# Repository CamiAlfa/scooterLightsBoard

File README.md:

# scooterLightsBoard
Add lights to the scooter

Board files designed using kicad 6.

The board uses the internal 12 volts to enable a relay.
That relay enables the stepdown and the front light.
The stepdown is a 4,5-60V LM2596HV. It must be regulated to 12v (or whatever voltage needed) before instalation to avoid damage.

The frontlight needs a separate switch to activate it independently.

The inputs of the board are:
* (J1) Drv signals:
  1. 12v signal
  2. Gnd
  3. Tail light signal
* (J2) Battery power:
  1. Batt +
  2. Batt -

The outputs are:
* (J3) Frontlight:
  1. Batt + (relay)
  2. 12v
  3. Gnd
* (J5) 12V output:
  1. 12v
  2. Gnd
* (j4) Tail light:
  1. Tail light+ (12v)
  2. Tail light-

Schematic for reference:

Greetings from Spain

Camilo

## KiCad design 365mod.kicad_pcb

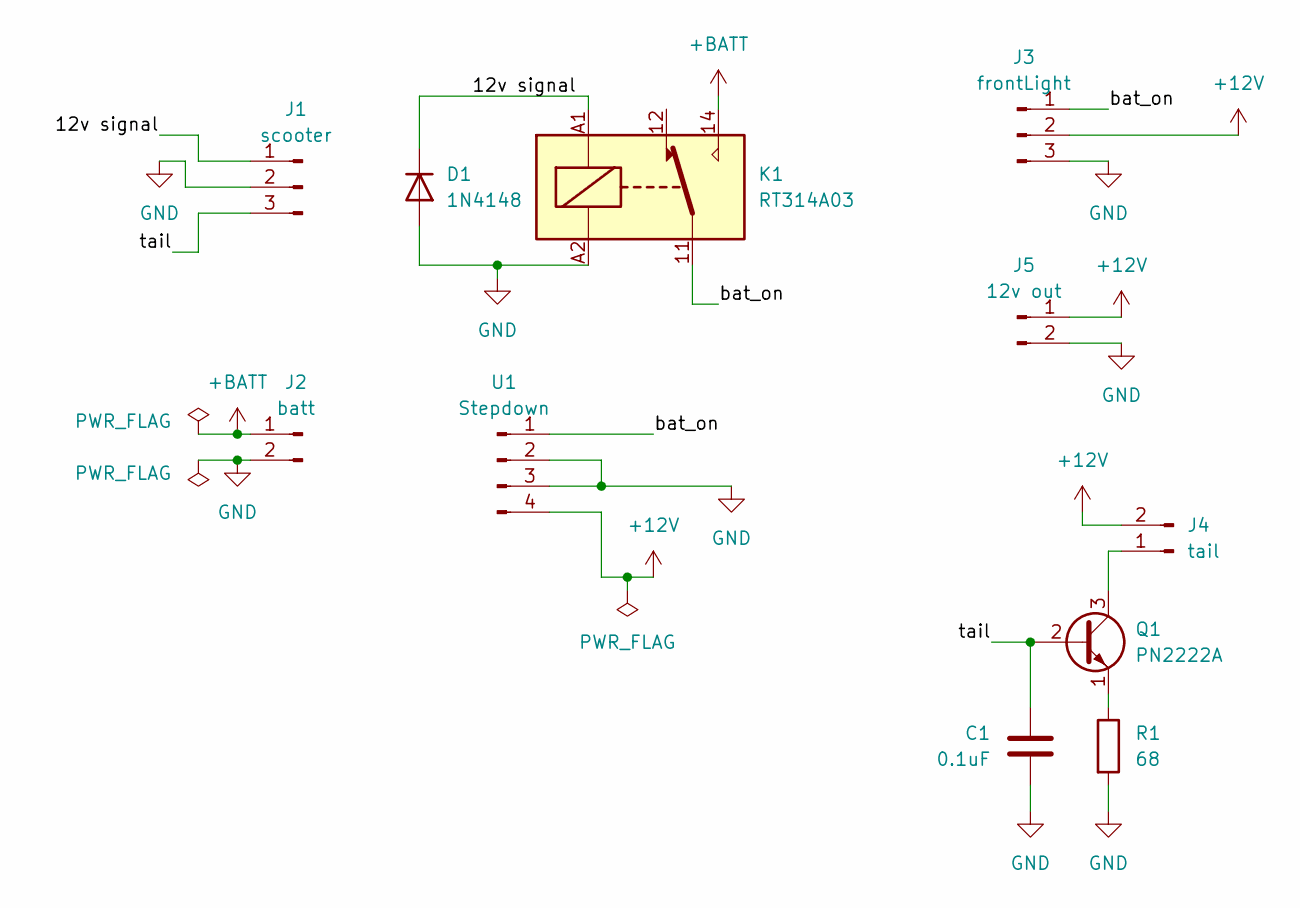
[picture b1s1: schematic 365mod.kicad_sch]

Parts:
C1: 0.1uF; C_Disc_D3.4mm_W2.1mm_P2.50mm
D1: 1N4148; D_DO-35_SOD27_P7.62mm_Horizontal
J1: scooter; PinHeader_1x03_P2.54mm_Vertical
J2: batt; PinHeader_1x02_P2.54mm_Vertical
J3: frontLight; PinHeader_1x03_P2.54mm_Vertical
J4: tail; PinHeader_1x02_P2.54mm_Vertical
J5: 12v out; PinHeader_1x02_P2.54mm_Vertical
K1: RT314A03; Relay_SPDT_Schrack-RT1-16A-FormC_RM5mm
Q1: PN2222A; TO-92_Inline
R1: 68; R_Axial_DIN0204_L3.6mm_D1.6mm_P2.54mm_Vertical
U1: Stepdown; DSN2596

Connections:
+12V: J3.2, J4.2, J5.1, U1.4
+BATT: J2.1, K1.14
/12v signal: D1.1 (K), J1.1, K1.A1
/bat_on: J3.1, K1.11, U1.1
/tail: C1.2, J1.3, Q1.2 (B)
GND: C1.1, D1.2 (A), J1.2, J2.2, J3.3, J5.2, K1.A2, R1.2, U1.2, U1.3
unnamed: J4.1, Q1.3 (C)
unnamed: Q1.1 (E), R1.1

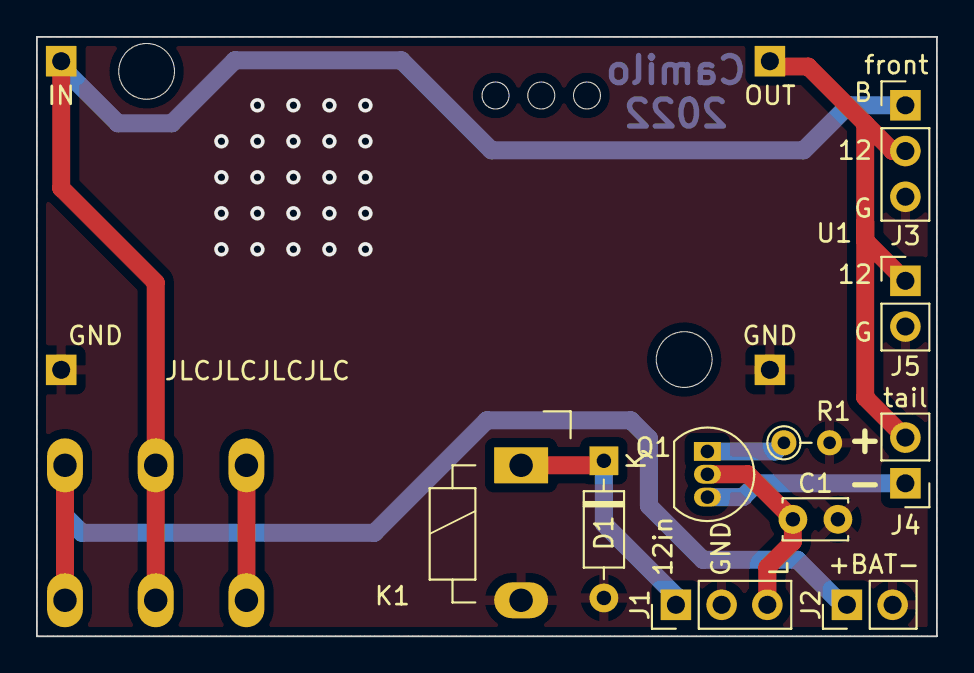
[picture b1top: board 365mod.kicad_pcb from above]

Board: 2 copper layers, 50.0 x 33.3 mm, 11 parts (0 on the bottom side), 8 nets.

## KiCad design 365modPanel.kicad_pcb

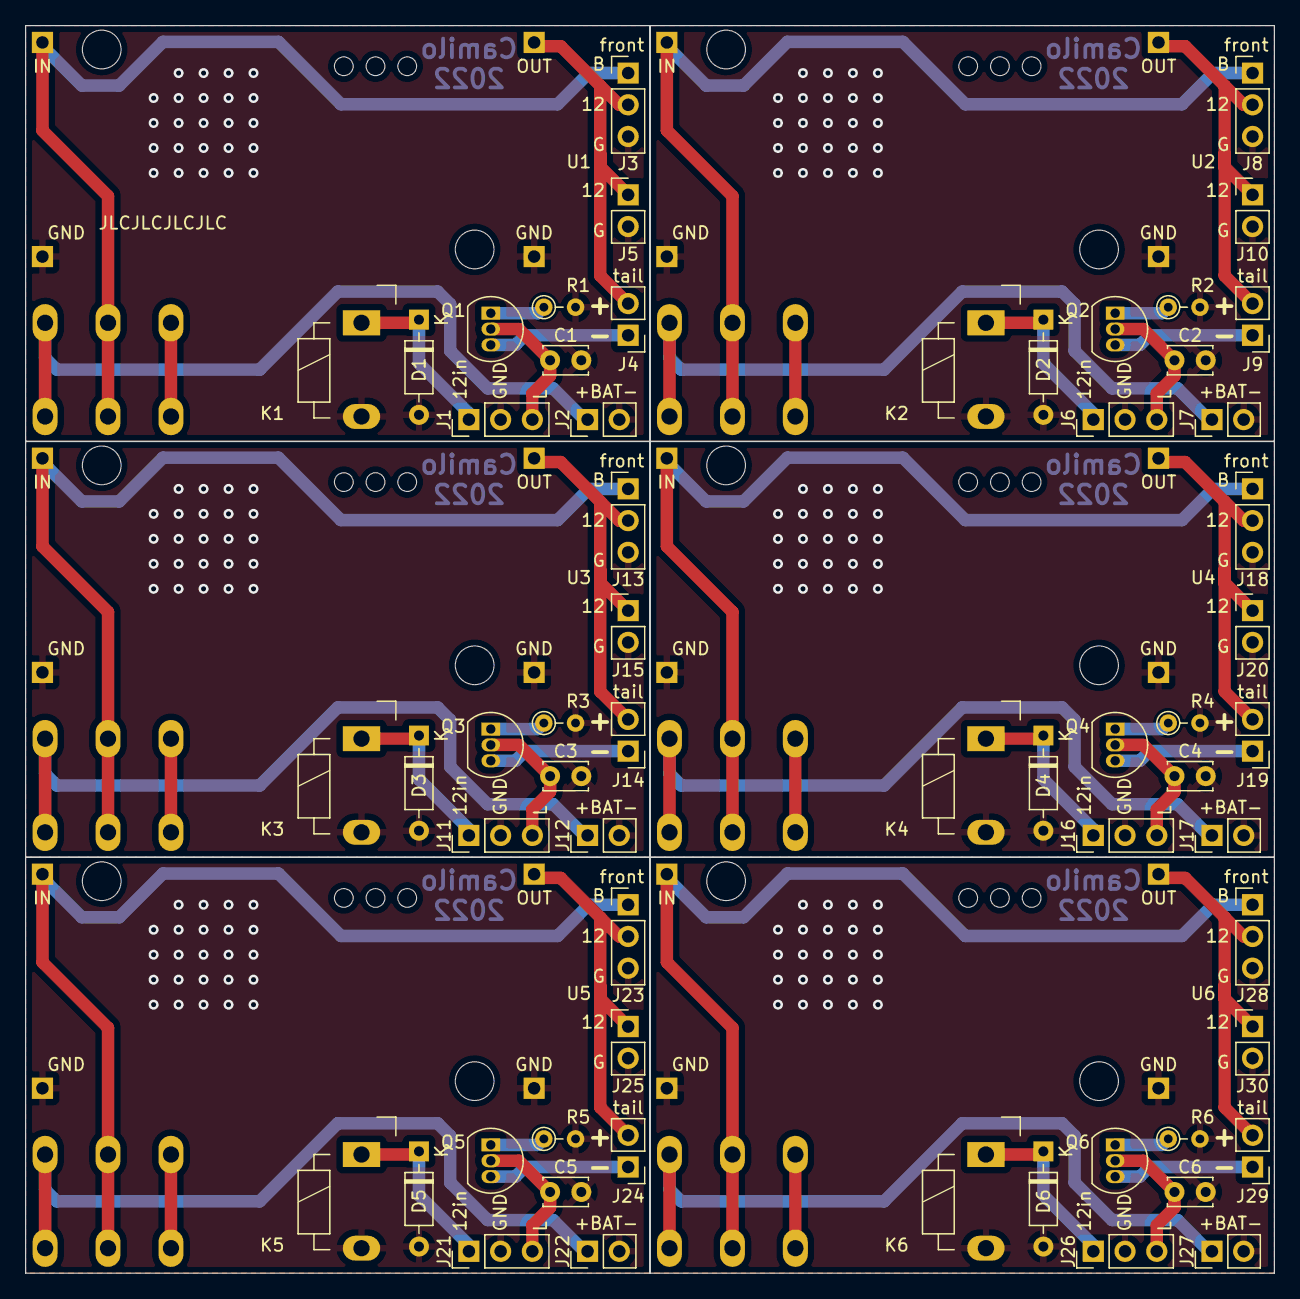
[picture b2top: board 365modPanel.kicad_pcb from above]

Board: 2 copper layers, 100.0 x 99.9 mm, 66 parts (0 on the bottom side), 8 nets.

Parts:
C1, C2, C3, C4, C5, C6: 0.1uF; C_Disc_D3.4mm_W2.1mm_P2.50mm
D1, D2, D3, D4, D5, D6: 1N4148; D_DO-35_SOD27_P7.62mm_Horizontal
J1, J6, J11, J16, J21, J26: scooter; PinHeader_1x03_P2.54mm_Vertical
J2, J7, J12, J17, J22, J27: batt; PinHeader_1x02_P2.54mm_Vertical
J3, J8, J13, J18, J23, J28: frontLight; PinHeader_1x03_P2.54mm_Vertical
J4, J9, J14, J19, J24, J29: tail; PinHeader_1x02_P2.54mm_Vertical
J5, J10, J15, J20, J25, J30: 12v out; PinHeader_1x02_P2.54mm_Vertical
K1, K2, K3, K4, K5, K6: RT314A03; Relay_SPDT_Schrack-RT1-16A-FormC_RM5mm
Q1, Q2, Q3, Q4, Q5, Q6: PN2222A; TO-92_Inline
R1, R2, R3, R4, R5, R6: 68; R_Axial_DIN0204_L3.6mm_D1.6mm_P2.54mm_Vertical
U1, U2, U3, U4, U5, U6: Stepdown; DSN2596

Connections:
+12V: J3.2, J4.2, J5.1, J8.2, J9.2, J10.1, J13.2, J14.2, J15.1, J18.2, J19.2, J20.1, J23.2, J24.2, J25.1, J28.2, J29.2, J30.1, U1.4, U2.4, U3.4, U4.4, U5.4, U6.4
+BATT: J2.1, J7.1, J12.1, J17.1, J22.1, J27.1, K1.14, K2.14, K3.14, K4.14, K5.14, K6.14
/12v signal: D1.1 (K), D2.1 (K), D3.1 (K), D4.1 (K), D5.1 (K), D6.1 (K), J1.1, J6.1, J11.1, J16.1, J21.1, J26.1, K1.A1, K2.A1, K3.A1, K4.A1, K5.A1, K6.A1
/bat_on: J3.1, J8.1, J13.1, J18.1, J23.1, J28.1, K1.11, K2.11, K3.11, K4.11, K5.11, K6.11, U1.1, U2.1, U3.1, U4.1, U5.1, U6.1
/tail: C1.2, C2.2, C3.2, C4.2, C5.2, C6.2, J1.3, J6.3, J11.3, J16.3, J21.3, J26.3, Q1.2 (B), Q2.2 (B), Q3.2 (B), Q4.2 (B), Q5.2 (B), Q6.2 (B)
GND: C1.1, C2.1, C3.1, C4.1, C5.1, C6.1, D1.2 (A), D2.2 (A), D3.2 (A), D4.2 (A), D5.2 (A), D6.2 (A), J1.2, J2.2, J3.3, J5.2, J6.2, J7.2, J8.3, J10.2, J11.2, J12.2, J13.3, J15.2, J16.2, J17.2, J18.3, J20.2, J21.2, J22.2, J23.3, J25.2, J26.2, J27.2, J28.3, J30.2, K1.A2, K2.A2, K3.A2, K4.A2, K5.A2, K6.A2, R1.2, R2.2, R3.2, R4.2, R5.2, R6.2, U1.2, U1.3, U2.2, U2.3, U3.2, U3.3, U4.2, U4.3, U5.2, U5.3, U6.2, U6.3
unnamed: J4.1, J9.1, J14.1, J19.1, J24.1, J29.1, Q1.3 (C), Q2.3 (C), Q3.3 (C), Q4.3 (C), Q5.3 (C), Q6.3 (C)
unnamed: Q1.1 (E), Q2.1 (E), Q3.1 (E), Q4.1 (E), Q5.1 (E), Q6.1 (E), R1.1, R2.1, R3.1, R4.1, R5.1, R6.1

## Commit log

2022-05-28 upload board
    upload file
2022-05-28 Create stepdown.bmp
    add stepdown image
